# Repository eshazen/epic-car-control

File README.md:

# epic-car-control

Arduino-based model car control for EPIC.  This is a PCB which mounts
on a model car used in the Partner Classes taught at EPIC.

* [Electronics Talk](https://docs.google.com/presentation/d/1JKn2IykLU-F7YahLROMGz_joYOWPTk3rvR12y0UCeqs/edit?usp=drive_link) -- Google doc link for summer 2023 talk
* [Software Development Log](SoftwareLog.md)
* [Wiring Diagram](Slides/wiring_diagram.pdf) -- how to wire the PCB to the car
* [Programming Instructions](Slides/car_program.pdf) -- instructions to change the target distance

## Hardware features

* Arduino pro micro socket
* MOSFET for motor control
* Optical sensor for wheel revolution counter
* Headlights and taillights with individual control
* Small speaker
* Bottom-mounted pushbutton switch for user inputs
* Screw terminal connectors for a 6V battery pack (4xAA) and motor
* Header connector for a power switch

## Software

Current software in `Arduino/car_control/car_control.ino`

```
power-up reads distance set from EEPROM
   long (error) beep means invalid setting (default to 5)
Idle mode
   short press - drive for programmed distance
   long press - move to 10's set mode
10's set mode
   short press: add 10 revs
   long press: to 1's set mode
1's set mode
   short press: add 1 revs
   long press: save setting and exit to IDLE
```

Current setting displayed in binary on LEDs as

| Location    | Value |
|:------------|:------|
| Right Front | 1     |
| Left Front  | 2     |
| Left Rear   | 4     |
| Right Rear  | 8     |

(value is sum of lit LEDs, or zero if all off)

Note that the current setting can be displayed with:

* **Long Press** - display 10's
* **Long Press** - display 1's
* **Long Press** - return to idle

Sensor test:

* Hold button while powering up
* Then press the button repeatedly:
  * first press: long beep, take reading, display low 4 bits
  * second press: display high 4 bits

Power down and up to exit test mode

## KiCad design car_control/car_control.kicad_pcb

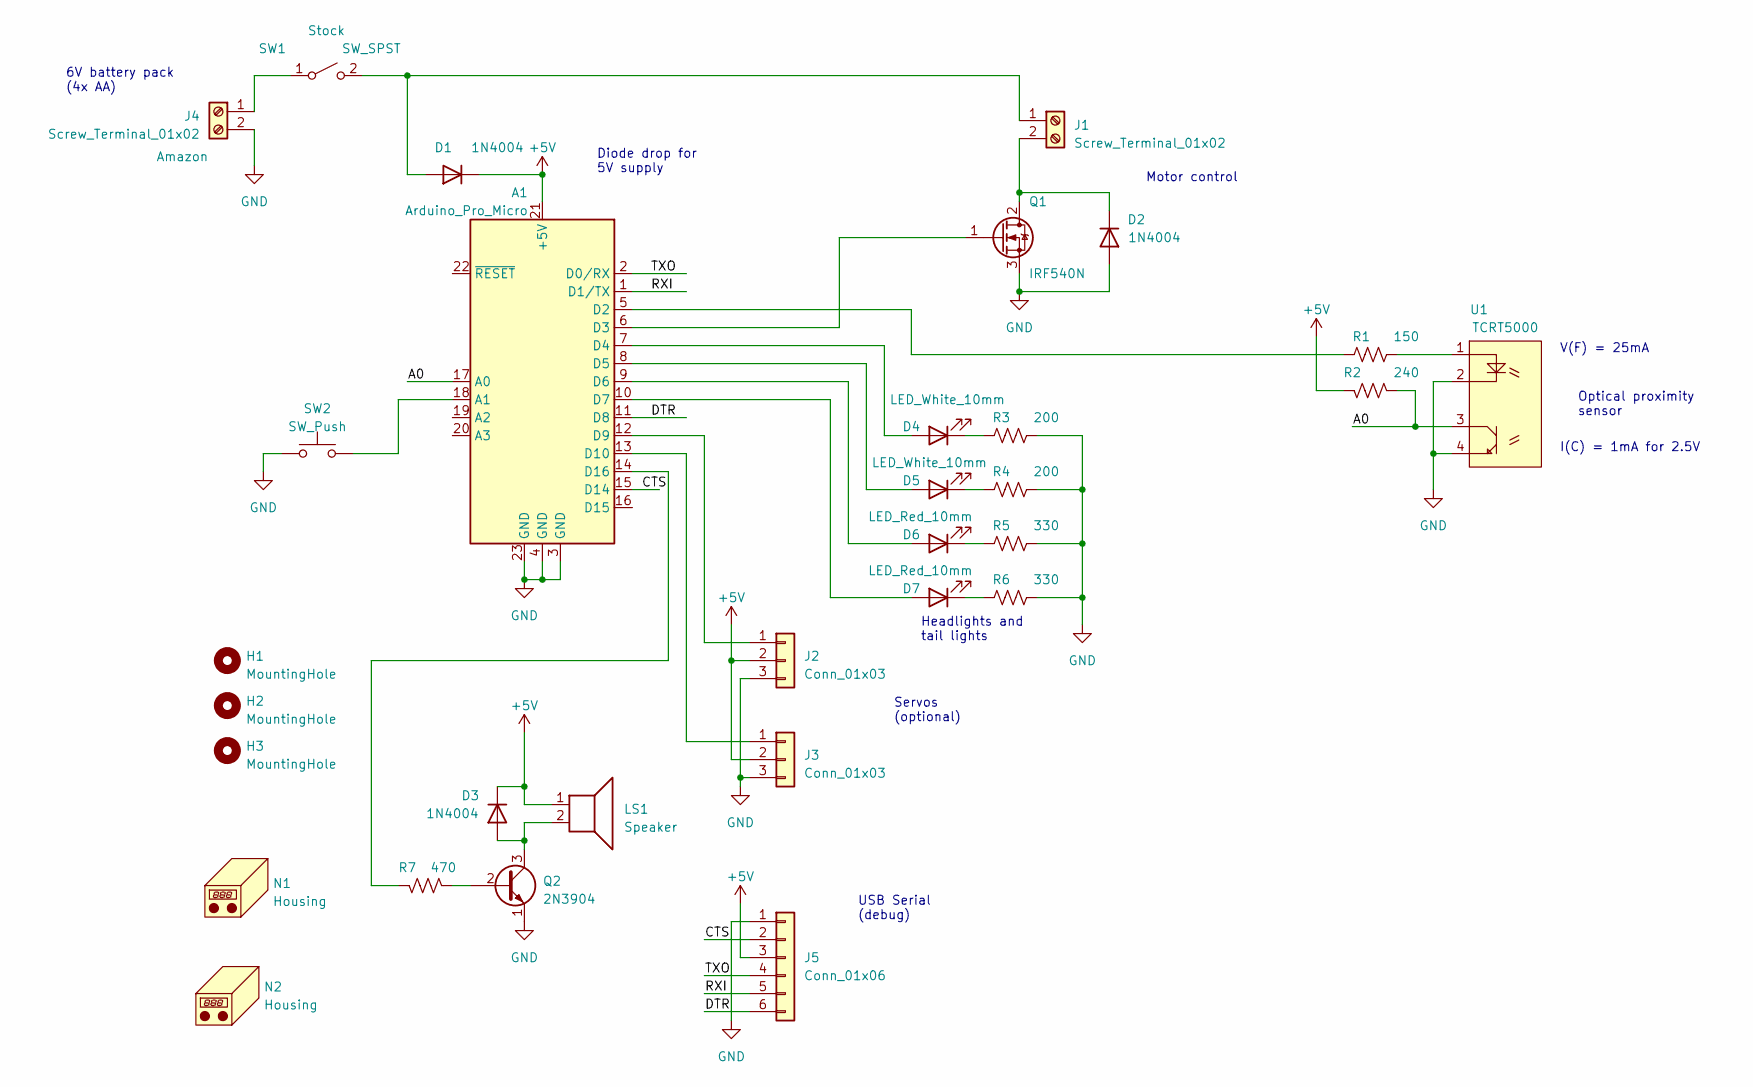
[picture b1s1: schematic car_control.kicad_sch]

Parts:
A1: Arduino_Pro_Micro; pro_micro_socket
D1, D2, D3: 1N4004; D_DO-41_SOD81_P10.16mm_Horizontal
D4, D5: LED_White_10mm; LED_D10.0mm_white
D6, D7: LED_Red_10mm; LED_D10.0mm_red
H1, H2, H3: MountingHole; MountingHole_2.7mm_M2.5_DIN965_Pad
J1, J4: Screw_Terminal_01x02; Wuerth_WR-WTB_64800211622_1x02_P1.50mm_Vertical
J2, J3: Conn_01x03; PinHeader_1x03_P2.54mm_Vertical
J5: Conn_01x06; PinHeader_1x06_P2.54mm_Vertical
LS1: Speaker; speaker_d12mm_h8.5_p6.5
N1: Housing; rhett_logo
N2: Housing; car_as
Q1: IRF540N; TO-220-3_Horizontal_TabDown
Q2: 2N3904; TO-92_Inline
R1: 150; R_Axial_DIN0207_L6.3mm_D2.5mm_P10.16mm_Horizontal
R2: 240; R_Axial_DIN0207_L6.3mm_D2.5mm_P10.16mm_Horizontal
R3, R4: 200; R_Axial_DIN0207_L6.3mm_D2.5mm_P10.16mm_Horizontal
R5, R6: 330; R_Axial_DIN0207_L6.3mm_D2.5mm_P10.16mm_Horizontal
R7: 470; R_Axial_DIN0207_L6.3mm_D2.5mm_P10.16mm_Horizontal
SW1: SW_SPST; PinHeader_1x02_P2.54mm_Vertical
SW2: SW_Push; SW_Cherry_MX_1.00u_PCB
U1: TCRT5000

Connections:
+5V: A1.21 (+5V), D1.1 (K), D3.1 (K), J2.2, J3.2, J5.3, LS1.1, R2.2
/A0: A1.17 (A0), R2.1, U1.3 (C)
/CTS: A1.15 (D14), J5.2
/DTR: A1.11 (D8), J5.6
/RXI: A1.1 (D1/TX), J5.5
/TXO: A1.2 (D0/RX), J5.4
GND: A1.3 (GND), A1.4 (GND), A1.23 (GND), D2.2 (A), J2.3, J3.3, J4.2, J5.1, Q1.3 (S), Q2.1 (E), R3.2, R4.2, R5.2, R6.2, SW2.1, U1.2 (C), U1.4 (E)
unnamed: A1.18 (A1), SW2.2
unnamed: A1.5 (D2), R1.1
unnamed: A1.6 (D3), Q1.1 (G)
unnamed: A1.7 (D4), D4.2 (A)
unnamed: A1.8 (D5), D5.2 (A)
unnamed: A1.9 (D6), D6.2 (A)
unnamed: A1.10 (D7), D7.2 (A)
unnamed: A1.12 (D9), J2.1
unnamed: A1.13 (D10), J3.1
unnamed: A1.14 (D16), R7.2
unnamed: D1.2 (A), J1.1, SW1.2 (B)
unnamed: D2.1 (K), J1.2, Q1.2 (D)
unnamed: D3.2 (A), LS1.2, Q2.3 (C)
unnamed: D4.1 (K), R3.1
unnamed: D5.1 (K), R4.1
unnamed: D6.1 (K), R5.1
unnamed: D7.1 (K), R6.1
unnamed: J4.1, SW1.1 (A)
unnamed: Q2.2 (B), R7.1
unnamed: R1.2, U1.1 (A)

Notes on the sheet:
6V battery pack (4x AA)
Diode drop for 5V supply
USB Serial (debug)
I(C) = 1mA for 2.5V
Optical proximity sensor
Servos (optional)
V(F) = 25mA
Motor control
Headlights and tail lights

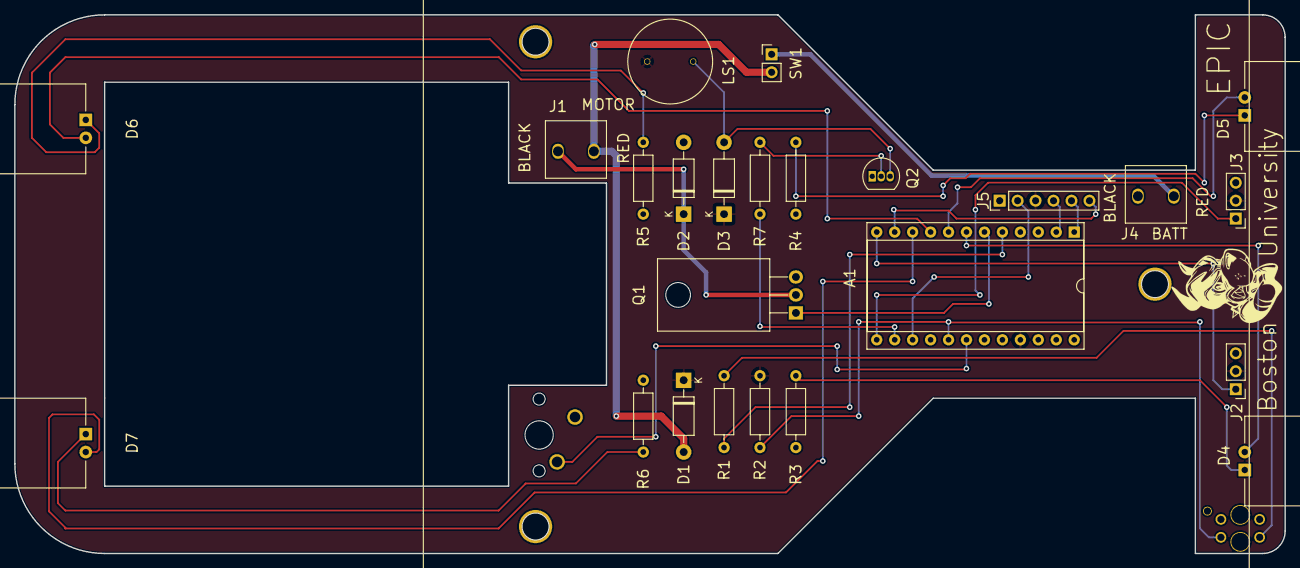
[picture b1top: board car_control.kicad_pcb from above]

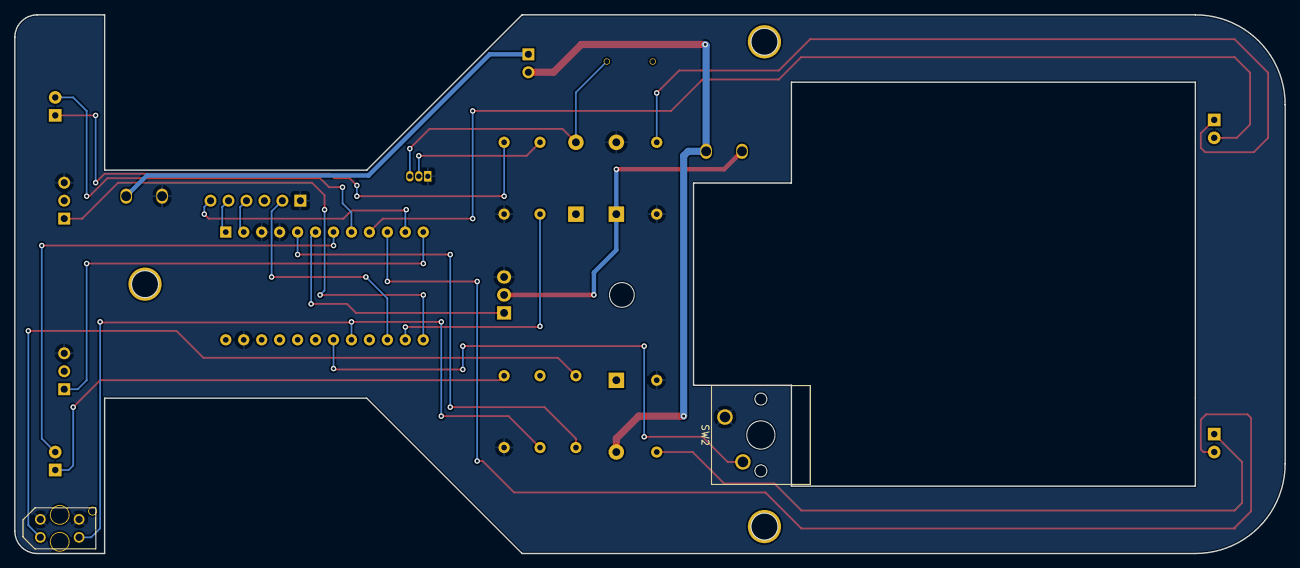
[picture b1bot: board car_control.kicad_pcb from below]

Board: 2 copper layers, 179.7 x 76.2 mm, 30 parts (2 on the bottom side), 27 nets.

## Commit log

2023-05-26 Initial schematic
2023-05-26 initial schematic done?
2023-05-26 working on mechanics
2023-05-27 working on PCB mechanics
2023-05-28 New board outline with wings
2023-05-28 candidate placement
2023-05-29 routing
2023-05-29 first version done?
2023-05-29 version 2 with tail
2023-05-30 Add USB serial connector
2023-05-30 Right angle 10mm headlights/tail lights
2023-05-30 playing with board outlines
2023-05-31 update board outline
2023-05-31 Updated PCB outline (PCB3) and adjust battery mount holes
2023-05-31 New board outline, LEDs need fixing
2023-05-31 add cherry switch, change pwr sw to header, reroute
2023-05-31 Rev 1 as built
2023-06-05 chassis revision
2023-06-09 add some preliminary software
2023-06-14 software
2023-06-15 add build list
2023-06-19 initial complete software
2023-06-19 LED display of values
2023-06-19 sensor test
2023-06-20 slides
2023-06-20 update initial power-up sequence
2023-06-21 working on setting LED blink
2023-06-21 programming
2023-06-21 tweaks
2023-06-21 tweak doco
2023-06-21 Fix spurious blinking. V5 release candidate
2023-06-23 diagrams
2023-06-27 image
2023-06-27 cleaning up
2023-06-27 notes and readme
2023-06-30 talk and slides
2023-06-30 V7 sensor code not yet working
2023-06-30 Rev 7 with sensor calibration
2023-07-20 programming update
2024-05-13 update docs
2024-05-14 Update doco for 2024
2024-05-29 testing instr
2024-05-29 pdf schem
2024-06-04 V8 software with sensor range increase to 1023
2024-06-06 update programming instructions
2024-06-18 docs
2024-06-18 update instructions
2025-02-14 starting on steering
2025-04-24 working on steering
2025-04-25 initial pass at steering parts
2025-05-29 Version 9 with EEPROM sensor limits fixed
2025-06-05 update doco for 2025
2025-06-05 update programming doc
2025-06-06 Rev 10 firmware to fix last (?) EEPROM bug
2025-06-09 updates for 2025
2025-06-09 software V10
